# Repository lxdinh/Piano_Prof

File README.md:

# CODING AGENTS: READ THIS FIRST

This is a **handoff bundle** from Claude Design (claude.ai/design).

A user mocked up designs in HTML/CSS/JS using an AI design tool, then exported this bundle so a coding agent can implement the designs for real.

## What you should do — IMPORTANT

**Read `piano-professor-v3/project/Piano Professor.html` in full.** The user had this file open when they triggered the handoff, so it's almost certainly the primary design they want built. Read it top to bottom — don't skim. Then **follow its imports**: open every file it pulls in (shared components, CSS, scripts) so you understand how the pieces fit together before you start implementing.

**If anything is ambiguous, ask the user to confirm before you start implementing.** It's much cheaper to clarify scope up front than to build the wrong thing.

## About the design files

The design medium is **HTML/CSS/JS** — these are prototypes, not production code. Your job is to **recreate them pixel-perfectly** in whatever technology makes sense for the target codebase (React, Vue, native, whatever fits). Match the visual output; don't copy the prototype's internal structure unless it happens to fit.

**Don't render these files in a browser or take screenshots unless the user asks you to.** Everything you need — dimensions, colors, layout rules — is spelled out in the source. Read the HTML and CSS directly; a screenshot won't tell you anything they don't.

## Bundle contents

- `piano-professor-v3/README.md` — this file
- `piano-professor-v3/project/` — the `Piano Professor V3` project files (HTML prototypes, assets, components)

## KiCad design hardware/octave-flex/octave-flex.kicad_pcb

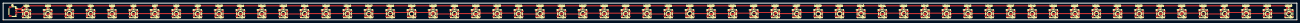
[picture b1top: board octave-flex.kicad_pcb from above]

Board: 2 copper layers, 831.3 x 10.7 mm, 121 parts (0 on the bottom side), 62 nets.

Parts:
C1, C2, C3, C4, C5, C6, C7, C8, C9, C10, C11, C12, C13, C14, C15, C16, C17, C18, C19, C20, C21, C22, C23, C24, C25, C26, C27, C28, C29, C30, C31, C32, C33, C34, C35, C36, C37, C38, C39, C40, C41, C42, C43, C44, C45, C46, C47, C48, C49, C50, C51, C52, C53, C54, C55, C56, C57, C58, C59, C60: 100nF; C_0603_1608Metric
J1: JST_SH_4P; JST_SH_SM04B-SRSS-TB_1x04-1MP_P1.00mm_Horizontal
LED1, LED2, LED3, LED4, LED5, LED6, LED7, LED8, LED9, LED10, LED11, LED12, LED13, LED14, LED15, LED16, LED17, LED18, LED19, LED20, LED21, LED22, LED23, LED24, LED25, LED26, LED27, LED28, LED29, LED30, LED31, LED32, LED33, LED34, LED35, LED36, LED37, LED38, LED39, LED40, LED41, LED42, LED43, LED44, LED45, LED46, LED47, LED48, LED49, LED50, LED51, LED52, LED53, LED54, LED55, LED56, LED57, LED58, LED59, LED60: WS2812B-B/W; LED-SMD_4P-L5.0-W5.0-TL_WS2812B-B

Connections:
+5V: C1.1, C2.1, C3.1, C4.1, C5.1, C6.1, C7.1, C8.1, C9.1, C10.1, C11.1, C12.1, C13.1, C14.1, C15.1, C16.1, C17.1, C18.1, C19.1, C20.1, C21.1, C22.1, C23.1, C24.1, C25.1, C26.1, C27.1, C28.1, C29.1, C30.1, C31.1, C32.1, C33.1, C34.1, C35.1, C36.1, C37.1, C38.1, C39.1, C40.1, C41.1, C42.1, C43.1, C44.1, C45.1, C46.1, C47.1, C48.1, C49.1, C50.1, C51.1, C52.1, C53.1, C54.1, C55.1, C56.1, C57.1, C58.1, C59.1, C60.1, J1.1, LED1.1 (VDD), LED2.1 (VDD), LED3.1 (VDD), LED4.1 (VDD), LED5.1 (VDD), LED6.1 (VDD), LED7.1 (VDD), LED8.1 (VDD), LED9.1 (VDD), LED10.1 (VDD), LED11.1 (VDD), LED12.1 (VDD), LED13.1 (VDD), LED14.1 (VDD), LED15.1 (VDD), LED16.1 (VDD), LED17.1 (VDD), LED18.1 (VDD), LED19.1 (VDD), LED20.1 (VDD), LED21.1 (VDD), LED22.1 (VDD), LED23.1 (VDD), LED24.1 (VDD), LED25.1 (VDD), LED26.1 (VDD), LED27.1 (VDD), LED28.1 (VDD), LED29.1 (VDD), LED30.1 (VDD), LED31.1 (VDD), LED32.1 (VDD), LED33.1 (VDD), LED34.1 (VDD), LED35.1 (VDD), LED36.1 (VDD), LED37.1 (VDD), LED38.1 (VDD), LED39.1 (VDD), LED40.1 (VDD), LED41.1 (VDD), LED42.1 (VDD), LED43.1 (VDD), LED44.1 (VDD), LED45.1 (VDD), LED46.1 (VDD), LED47.1 (VDD), LED48.1 (VDD), LED49.1 (VDD), LED50.1 (VDD), LED51.1 (VDD), LED52.1 (VDD), LED53.1 (VDD), LED54.1 (VDD), LED55.1 (VDD), LED56.1 (VDD), LED57.1 (VDD), LED58.1 (VDD), LED59.1 (VDD), LED60.1 (VDD)
/DIN_IN: J1.3, LED1.4 (DIN)
GND: C1.2, C2.2, C3.2, C4.2, C5.2, C6.2, C7.2, C8.2, C9.2, C10.2, C11.2, C12.2, C13.2, C14.2, C15.2, C16.2, C17.2, C18.2, C19.2, C20.2, C21.2, C22.2, C23.2, C24.2, C25.2, C26.2, C27.2, C28.2, C29.2, C30.2, C31.2, C32.2, C33.2, C34.2, C35.2, C36.2, C37.2, C38.2, C39.2, C40.2, C41.2, C42.2, C43.2, C44.2, C45.2, C46.2, C47.2, C48.2, C49.2, C50.2, C51.2, C52.2, C53.2, C54.2, C55.2, C56.2, C57.2, C58.2, C59.2, C60.2, J1.2, LED1.3 (VSS), LED2.3 (VSS), LED3.3 (VSS), LED4.3 (VSS), LED5.3 (VSS), LED6.3 (VSS), LED7.3 (VSS), LED8.3 (VSS), LED9.3 (VSS), LED10.3 (VSS), LED11.3 (VSS), LED12.3 (VSS), LED13.3 (VSS), LED14.3 (VSS), LED15.3 (VSS), LED16.3 (VSS), LED17.3 (VSS), LED18.3 (VSS), LED19.3 (VSS), LED20.3 (VSS), LED21.3 (VSS), LED22.3 (VSS), LED23.3 (VSS), LED24.3 (VSS), LED25.3 (VSS), LED26.3 (VSS), LED27.3 (VSS), LED28.3 (VSS), LED29.3 (VSS), LED30.3 (VSS), LED31.3 (VSS), LED32.3 (VSS), LED33.3 (VSS), LED34.3 (VSS), LED35.3 (VSS), LED36.3 (VSS), LED37.3 (VSS), LED38.3 (VSS), LED39.3 (VSS), LED40.3 (VSS), LED41.3 (VSS), LED42.3 (VSS), LED43.3 (VSS), LED44.3 (VSS), LED45.3 (VSS), LED46.3 (VSS), LED47.3 (VSS), LED48.3 (VSS), LED49.3 (VSS), LED50.3 (VSS), LED51.3 (VSS), LED52.3 (VSS), LED53.3 (VSS), LED54.3 (VSS), LED55.3 (VSS), LED56.3 (VSS), LED57.3 (VSS), LED58.3 (VSS), LED59.3 (VSS), LED60.3 (VSS)
unnamed: LED1.2 (DOUT), LED2.4 (DIN)
unnamed: LED2.2 (DOUT), LED3.4 (DIN)
unnamed: LED3.2 (DOUT), LED4.4 (DIN)
unnamed: LED4.2 (DOUT), LED5.4 (DIN)
unnamed: LED5.2 (DOUT), LED6.4 (DIN)
unnamed: LED6.2 (DOUT), LED7.4 (DIN)
unnamed: LED7.2 (DOUT), LED8.4 (DIN)
unnamed: LED8.2 (DOUT), LED9.4 (DIN)
unnamed: LED9.2 (DOUT), LED10.4 (DIN)
unnamed: LED10.2 (DOUT), LED11.4 (DIN)
unnamed: LED11.2 (DOUT), LED12.4 (DIN)
unnamed: LED12.2 (DOUT), LED13.4 (DIN)
unnamed: LED13.2 (DOUT), LED14.4 (DIN)
unnamed: LED14.2 (DOUT), LED15.4 (DIN)
unnamed: LED15.2 (DOUT), LED16.4 (DIN)
unnamed: LED16.2 (DOUT), LED17.4 (DIN)
unnamed: LED17.2 (DOUT), LED18.4 (DIN)
unnamed: LED18.2 (DOUT), LED19.4 (DIN)
unnamed: LED19.2 (DOUT), LED20.4 (DIN)
unnamed: LED20.2 (DOUT), LED21.4 (DIN)
unnamed: LED21.2 (DOUT), LED22.4 (DIN)
unnamed: LED22.2 (DOUT), LED23.4 (DIN)
unnamed: LED23.2 (DOUT), LED24.4 (DIN)
unnamed: LED24.2 (DOUT), LED25.4 (DIN)
unnamed: LED25.2 (DOUT), LED26.4 (DIN)
unnamed: LED26.2 (DOUT), LED27.4 (DIN)
unnamed: LED27.2 (DOUT), LED28.4 (DIN)
unnamed: LED28.2 (DOUT), LED29.4 (DIN)
unnamed: LED29.2 (DOUT), LED30.4 (DIN)
unnamed: LED30.2 (DOUT), LED31.4 (DIN)
unnamed: LED31.2 (DOUT), LED32.4 (DIN)
unnamed: LED32.2 (DOUT), LED33.4 (DIN)
unnamed: LED33.2 (DOUT), LED34.4 (DIN)
unnamed: LED34.2 (DOUT), LED35.4 (DIN)
unnamed: LED35.2 (DOUT), LED36.4 (DIN)
unnamed: LED36.2 (DOUT), LED37.4 (DIN)
unnamed: LED37.2 (DOUT), LED38.4 (DIN)
unnamed: LED38.2 (DOUT), LED39.4 (DIN)
unnamed: LED39.2 (DOUT), LED40.4 (DIN)
unnamed: LED40.2 (DOUT), LED41.4 (DIN)
unnamed: LED41.2 (DOUT), LED42.4 (DIN)
unnamed: LED42.2 (DOUT), LED43.4 (DIN)
unnamed: LED43.2 (DOUT), LED44.4 (DIN)
unnamed: LED44.2 (DOUT), LED45.4 (DIN)
unnamed: LED45.2 (DOUT), LED46.4 (DIN)
unnamed: LED46.2 (DOUT), LED47.4 (DIN)
unnamed: LED47.2 (DOUT), LED48.4 (DIN)
unnamed: LED48.2 (DOUT), LED49.4 (DIN)
unnamed: LED49.2 (DOUT), LED50.4 (DIN)
unnamed: LED50.2 (DOUT), LED51.4 (DIN)
unnamed: LED51.2 (DOUT), LED52.4 (DIN)
unnamed: LED52.2 (DOUT), LED53.4 (DIN)
unnamed: LED53.2 (DOUT), LED54.4 (DIN)
unnamed: LED54.2 (DOUT), LED55.4 (DIN)
unnamed: LED55.2 (DOUT), LED56.4 (DIN)
unnamed: LED56.2 (DOUT), LED57.4 (DIN)
unnamed: LED57.2 (DOUT), LED58.4 (DIN)
unnamed: LED58.2 (DOUT), LED59.4 (DIN)
unnamed: LED59.2 (DOUT), LED60.4 (DIN)

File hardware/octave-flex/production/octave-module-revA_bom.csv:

Designator,Footprint,Quantity,Value,LCSC Part #
"C1, C10, C11, C12, C13, C14, C15, C16, C17, C18, C19, C2, C20, C21, C22, C23, C24, C25, C26, C27, C28, C29, C3, C30, C31, C32, C33, C34, C35, C36, C37, C38, C39, C4, C40, C41, C42, C43, C44, C45, C46, C47, C48, C49, C5, C50, C51, C52, C53, C54, C55, C56, C57, C58, C59, C6, C60, C7, C8, C9",0603,60,100nF,C14663
J1,JST_SH_SM04B-SRSS-TB_1x04-1MP_P1.00mm_Horizontal,1,JST_SH_4P,C160404
"LED1, LED10, LED11, LED12, LED13, LED14, LED15, LED16, LED17, LED18, LED19, LED2, LED20, LED21, LED22, LED23, LED24, LED25, LED26, LED27, LED28, LED29, LED3, LED30, LED31, LED32, LED33, LED34, LED35, LED36, LED37, LED38, LED39, LED4, LED40, LED41, LED42, LED43, LED44, LED45, LED46, LED47, LED48, LED49, LED5, LED50, LED51, LED52, LED53, LED54, LED55, LED56, LED57, LED58, LED59, LED6, LED60, LED7, LED8, LED9",LED-SMD_4P-L5.0-W5.0-TL_WS2812B-B,60,WS2812B-B/W,C114586

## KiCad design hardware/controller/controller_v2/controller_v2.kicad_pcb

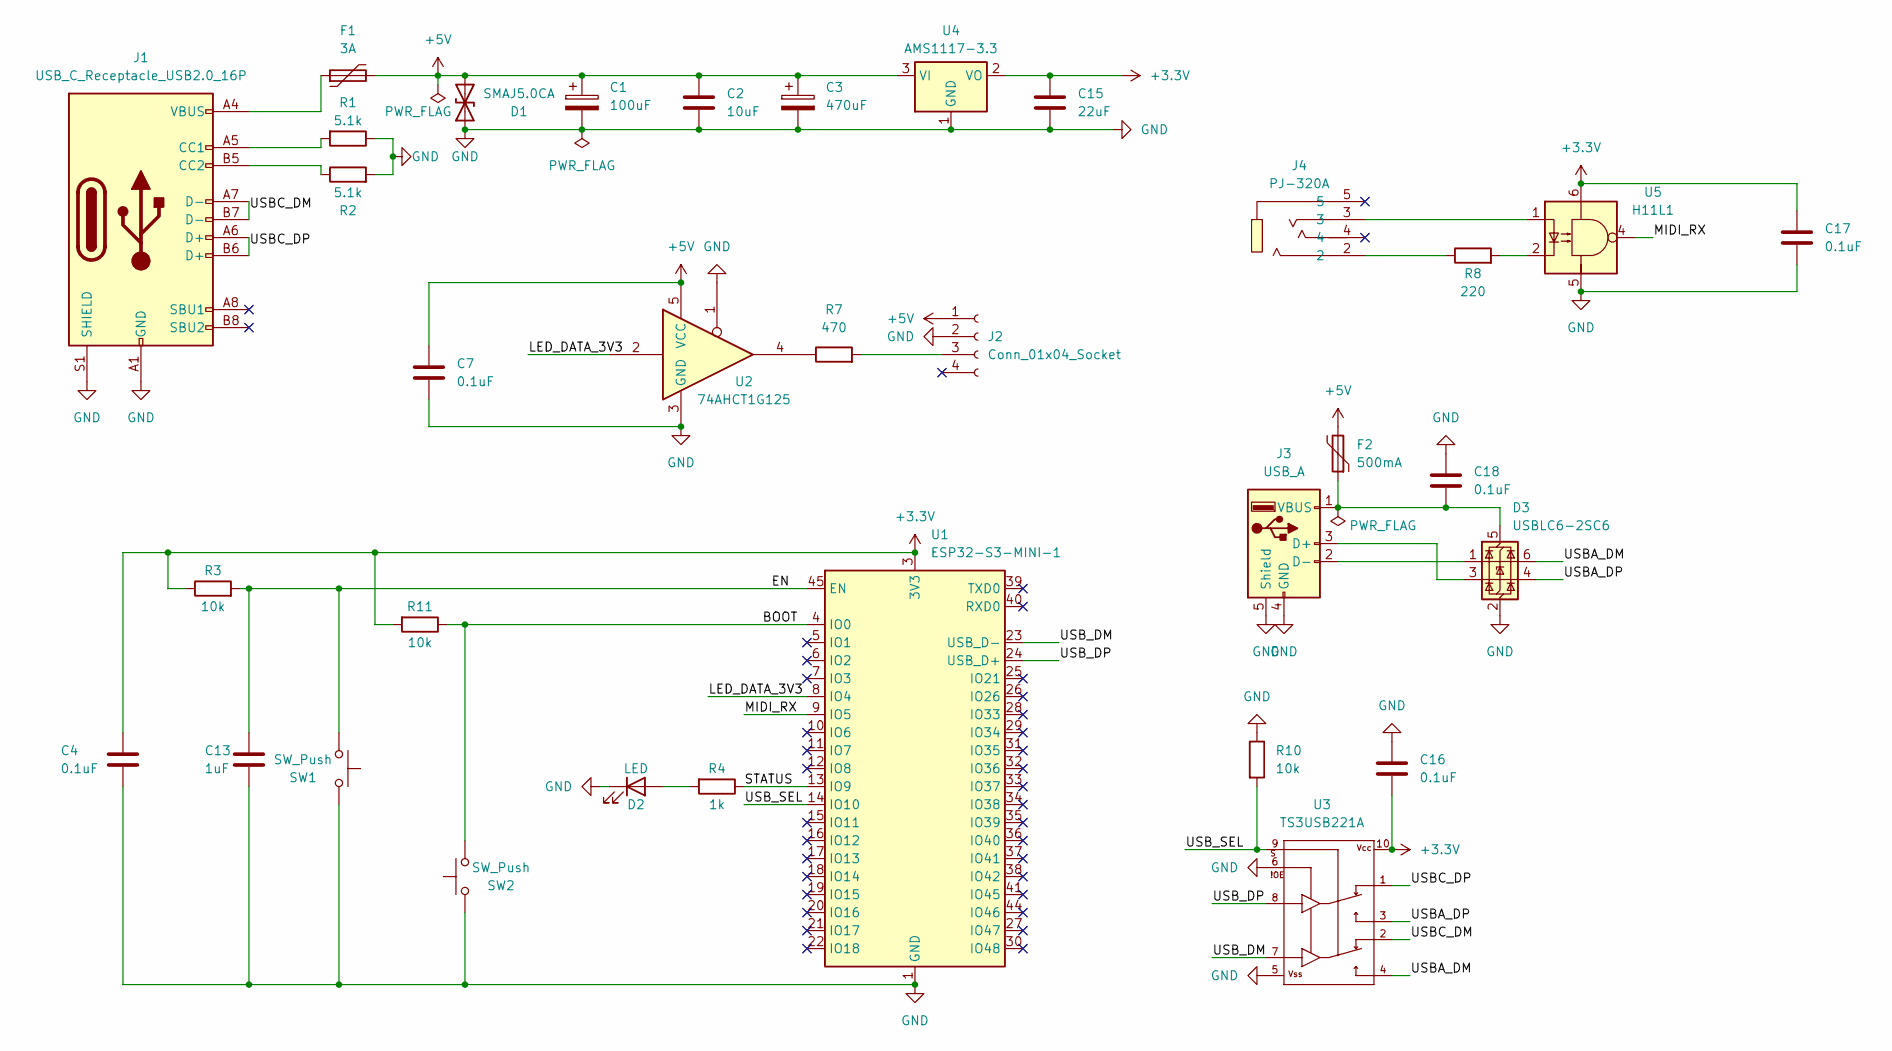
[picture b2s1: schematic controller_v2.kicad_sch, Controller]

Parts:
C1: 100uF; CP_Elec_6.3x5.4
C2: 10uF; C_0805_2012Metric
C3: 470uF; CP_Elec_8x10.5
C4, C7, C16, C17, C18: 0.1uF; C_0603_1608Metric
C13: 1uF; C_0603_1608Metric
C15: 22uF; C_0805_2012Metric
D1: SMAJ5.0CA; D_SMA
D2: LED; LED_0603_1608Metric
D3: USBLC6-2SC6; SOT-23-6
F1: 3A; Fuse_1812_4532Metric
F2: 500mA; Fuse_1206_3216Metric
J1: USB_C_Receptacle_USB2.0_16P; USB_C_Receptacle_GCT_USB4105-xx-A_16P_TopMnt_Horizontal
J2: Conn_01x04_Socket; JST_SH_SM04B-SRSS-TB_1x04-1MP_P1.00mm_Horizontal
J3: USB_A; USB_A_TE_292303-7_Horizontal
J4: PJ-320A; AUDIO-TH_XKB_PJ-320A; MPN PJ-320A; LCSC Part C2884926
R1, R2: 5.1k; R_0603_1608Metric
R3, R10, R11: 10k; R_0603_1608Metric
R4: 1k; R_0603_1608Metric
R7: 470; R_0603_1608Metric
R8: 220; R_0603_1608Metric
SW1, SW2: SW_Push; SW_SPST_PTS645Sx43SMTR92
U1: ESP32-S3-MINI-1; ESP32-S2-MINI-1
U2: 74AHCT1G125; SOT-23-5
U3: TS3USB221A; QFN-10-RSE
U4: AMS1117-3.3; SOT-223-3_TabPin2
U5: H11L1; IC_H11L1SM

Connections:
+3.3V: C4.1, C15.1, C16.2, C17.2, R3.1, R11.2, U1.3 (3V3), U3.10, U4.2 (VO), U5.6; also elsewhere on the board
+5V: C1.1, C2.1, C3.1, C7.1, D1.2 (A2), F1.2, F2.2, J2.1, U2.5 (VCC), U4.3 (VI)
/BOOT: R11.1, SW2.2, U1.4 (IO0)
/EN: C13.1, R3.2, SW1.1, U1.45 (EN)
/LED_DATA_3V3: U1.8 (IO4), U2.2
/MIDI_RX: U1.9 (IO5), U5.4; also elsewhere on the board
/STATUS: R4.1, U1.13 (IO9)
/USBA_DM: D3.6 (I/O1), U3.4
/USBA_DP: D3.4 (I/O2), U3.3
/USBC_DM: J1.A7 (D-), J1.B7 (D-), U3.2
/USBC_DP: J1.A6 (D+), J1.B6 (D+), U3.1
/USB_DM: U1.23 (USB_D-), U3.7
/USB_DP: U1.24 (USB_D+), U3.8
/USB_SEL: R10.2, U1.14 (IO10), U3.9
GND: C1.2, C2.2, C3.2, C4.2, C7.2, C13.2, C15.2, C16.1, C17.1, C18.2, D1.1 (A1), D2.1 (K), D3.2 (GND), J1.A1 (GND), J1.A12 (GND), J1.B1 (GND), J1.B12 (GND), J1.S1 (SHIELD), J2.2, J3.4 (GND), J3.5 (Shield), R1.1, R2.2, R10.1, SW1.2, SW2.1, U1.1 (GND), U1.2 (GND), U1.42 (GND), U1.43 (GND), U1.46 (GND), U1.47 (GND), U1.48 (GND), U1.49 (GND), U1.50 (GND), U1.51 (GND), U1.52 (GND), U1.53 (GND), U1.54 (GND), U1.55 (GND), U1.56 (GND), U1.57 (GND), U1.58 (GND), U1.59 (GND), U1.60 (GND), U1.61 (GND), U1.62 (GND), U1.63 (GND), U1.64 (GND), U1.65 (GND), U2.1, U2.3 (GND), U3.5, U3.6, U4.1 (GND), U5.5
unnamed: D2.2 (A), R4.2
unnamed: C18.1, D3.5 (VBUS), F2.1, J3.1 (VBUS)
unnamed: F1.1, J1.A4 (VBUS), J1.A9 (VBUS), J1.B4 (VBUS), J1.B9 (VBUS)
unnamed: J1.A5 (CC1), R1.2
unnamed: J1.B5 (CC2), R2.1
unnamed: J2.3, R7.2
unnamed: D3.3 (I/O2), J3.3 (D+)
unnamed: D3.1 (I/O1), J3.2 (D-)
unnamed: J4.2, R8.1
unnamed: J4.3, U5.1
unnamed: R7.1, U2.4
unnamed: R8.2, U5.2

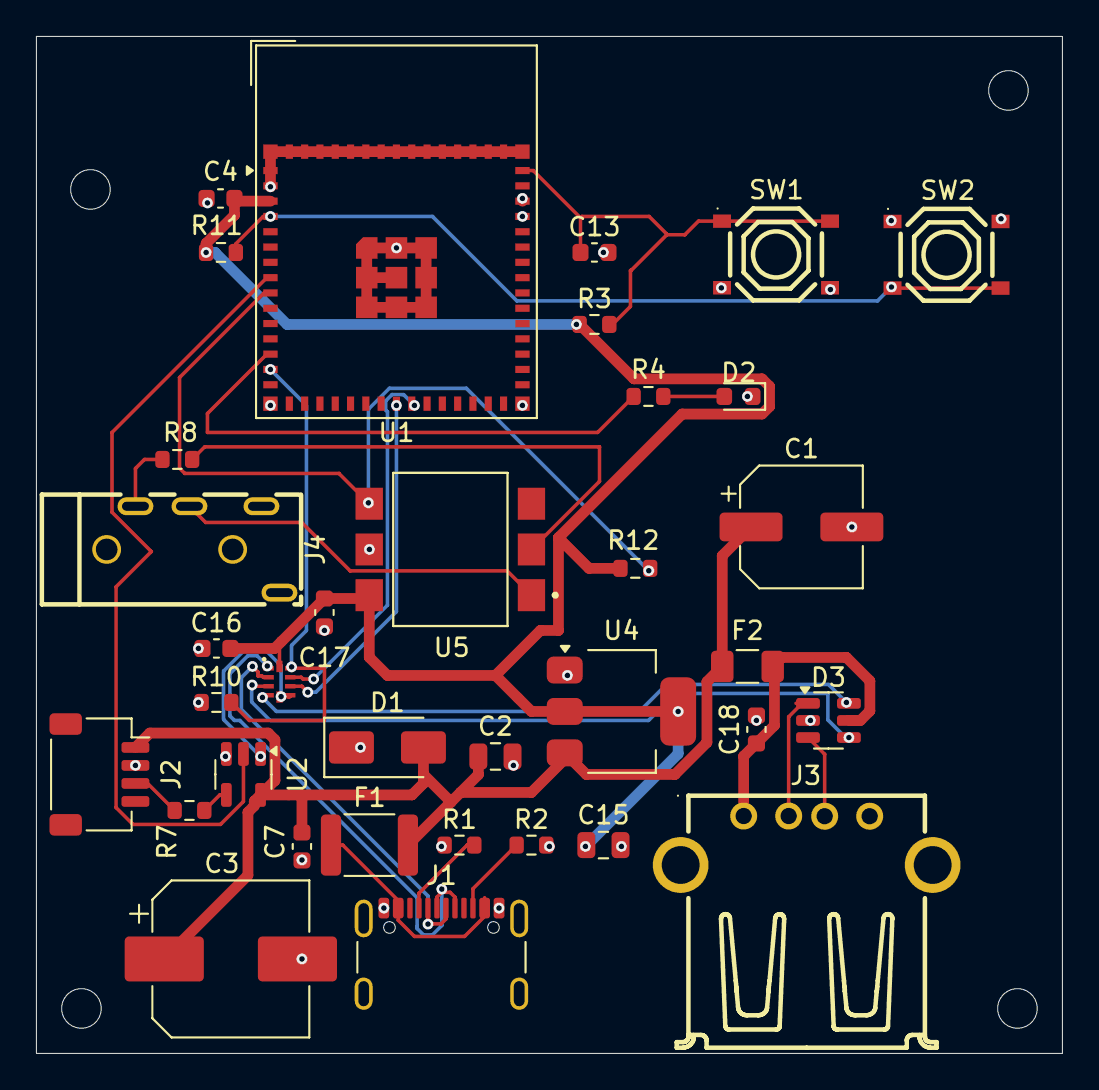
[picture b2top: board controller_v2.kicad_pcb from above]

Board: 2 copper layers, 57.0 x 56.5 mm, 35 parts (0 on the bottom side), 27 nets.

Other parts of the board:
R12: 1k; R_0603_1608Metric

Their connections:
+3.3V: R12.1; also elsewhere on the board
/MIDI_RX: R12.2; also elsewhere on the board

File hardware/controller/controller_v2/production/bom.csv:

Designator,Footprint,Quantity,Value,LCSC Part #
C1,CP_Elec_6.3x5.4,1,100uF,C44638
C13,0603,1,1uF,C15849
C15,0805,1,22uF,C45783
"C16, C17, C18, C4, C7",0603,5,0.1uF,C14663
C2,0805,1,10uF,C15850
C3,CP_Elec_8x10.5,1,470uF,C42599
D1,D_SMA,1,SMAJ5.0CA,C202221
D2,0603,1,LED,C72043
D3,SOT-23-6,1,USBLC6-2SC6,C7519
F1,1812,1,3A,C190053
F2,1206,1,500mA,C106264
J1,USB_C_Receptacle_GCT_USB4105-xx-A_16P_TopMnt_Horizontal,1,USB_C_Receptacle_USB2.0_16P,C165948
J2,JST_SH_SM04B-SRSS-TB_1x04-1MP_P1.00mm_Horizontal,1,Conn_01x04_Socket,C160403
J3,USB_A_TE_292303-7_Horizontal,1,USB_A,C86461
J4,AUDIO-TH_XKB_PJ-320A,1,PJ-320A,C2884926
"R1, R2",0603,2,5.1k,C23186
"R10, R11, R3",0603,3,10k,C25804
R4,0603,1,1k,C21190
R7,0603,1,470,C23179
R8,0603,1,220,C22962
"SW1, SW2",SW_SPST_PTS645Sx43SMTR92,2,SW_Push,C318884
U1,ESP32-S2-MINI-1,1,ESP32-S3-MINI-1,C3013941
U2,SOT-23-5,1,74AHCT1G125,C7484
U3,QFN-10-RSE,1,TS3USB221A,C128396
U4,SOT-223-3_TabPin2,1,AMS1117-3.3,C6186
U5,IC_H11L1SM,1,H11L1,C78589

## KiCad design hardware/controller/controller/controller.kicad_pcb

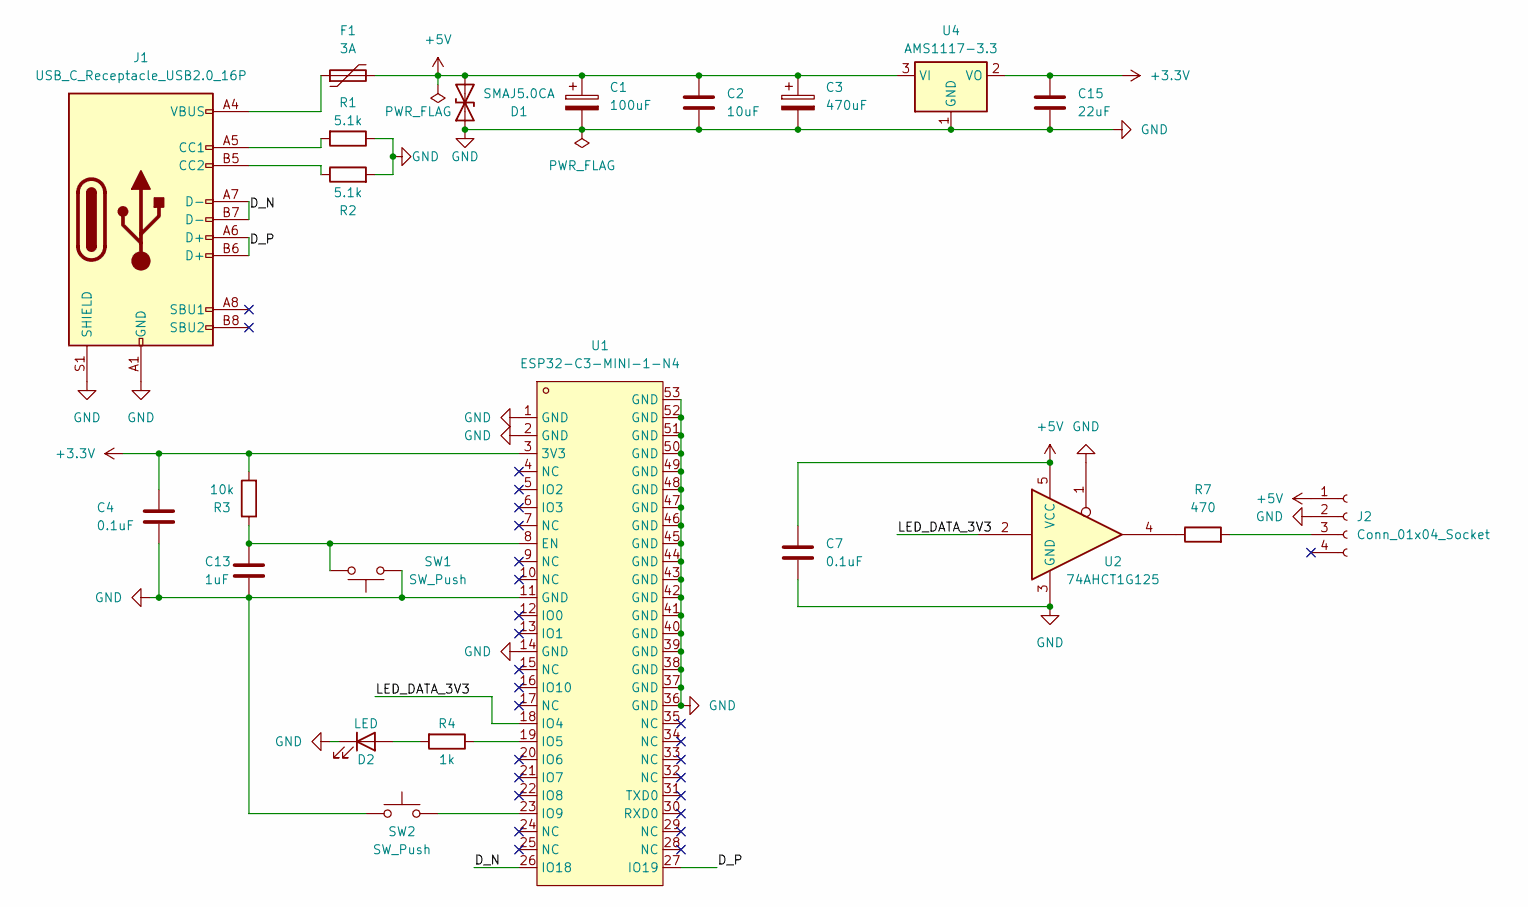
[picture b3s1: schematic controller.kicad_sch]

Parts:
C1: 100uF; CP_Elec_6.3x5.4
C2: 10uF; C_0805_2012Metric
C3: 470uF; CP_Elec_8x10.5
C4, C7: 0.1uF; C_0603_1608Metric
C13: 1uF; C_0603_1608Metric
C15: 22uF; C_0805_2012Metric
D1: SMAJ5.0CA; D_SMA
D2: LED; LED_0603_1608Metric
F1: 3A; Fuse_1812_4532Metric
J1: USB_C_Receptacle_USB2.0_16P; USB_C_Receptacle_GCT_USB4105-xx-A_16P_TopMnt_Horizontal
J2: Conn_01x04_Socket; JST_SH_SM04B-SRSS-TB_1x04-1MP_P1.00mm_Horizontal
R1, R2: 5.1k; R_0603_1608Metric
R3: 10k; R_0603_1608Metric
R4: 1k; R_0603_1608Metric
R7: 470; R_0603_1608Metric
SW1, SW2: SW_Push; SW_SPST_PTS645Sx43SMTR92
U1: ESP32-C3-MINI-1-N4; WIFIM-SMD_ESP32-C3-MINI-1; MPN ESP32-C3-MINI-1-N4; LCSC Part C2838502
U2: 74AHCT1G125; SOT-23-5
U4: AMS1117-3.3; SOT-223-3_TabPin2

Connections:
+3.3V: C4.1, C15.1, R3.2, U1.3 (3V3), U4.2 (VO)
+5V: C1.1, C2.1, C3.1, C7.1, D1.2 (A2), F1.2, J2.1, U2.5 (VCC), U4.3 (VI)
/D_N: J1.A7 (D-), J1.B7 (D-), U1.26 (IO18)
/D_P: J1.A6 (D+), J1.B6 (D+), U1.27 (IO19)
/LED_DATA_3V3: U1.18 (IO4), U2.2
GND: C1.2, C2.2, C3.2, C4.2, C7.2, C13.2, C15.2, D1.1 (A1), D2.1 (K), J1.A1 (GND), J1.A12 (GND), J1.B1 (GND), J1.B12 (GND), J1.S1 (SHIELD), J2.2, R1.1, R2.2, SW1.1, SW2.1, U1.1 (GND), U1.2 (GND), U1.11 (GND), U1.14 (GND), U1.36 (GND), U1.37 (GND), U1.38 (GND), U1.39 (GND), U1.40 (GND), U1.41 (GND), U1.42 (GND), U1.43 (GND), U1.44 (GND), U1.45 (GND), U1.46 (GND), U1.47 (GND), U1.48 (GND), U1.49 (GND), U1.50 (GND), U1.51 (GND), U1.52 (GND), U1.53 (GND), U2.1, U2.3 (GND), U4.1 (GND)
unnamed: D2.2 (A), R4.2
unnamed: F1.1, J1.A4 (VBUS), J1.A9 (VBUS), J1.B4 (VBUS), J1.B9 (VBUS)
unnamed: J1.A5 (CC1), R1.2
unnamed: J1.B5 (CC2), R2.1
unnamed: J2.3, R7.2
unnamed: R7.1, U2.4
unnamed: C13.1, R3.1, SW1.2, U1.8 (EN)
unnamed: R4.1, U1.19 (IO5)
unnamed: SW2.2, U1.23 (IO9)

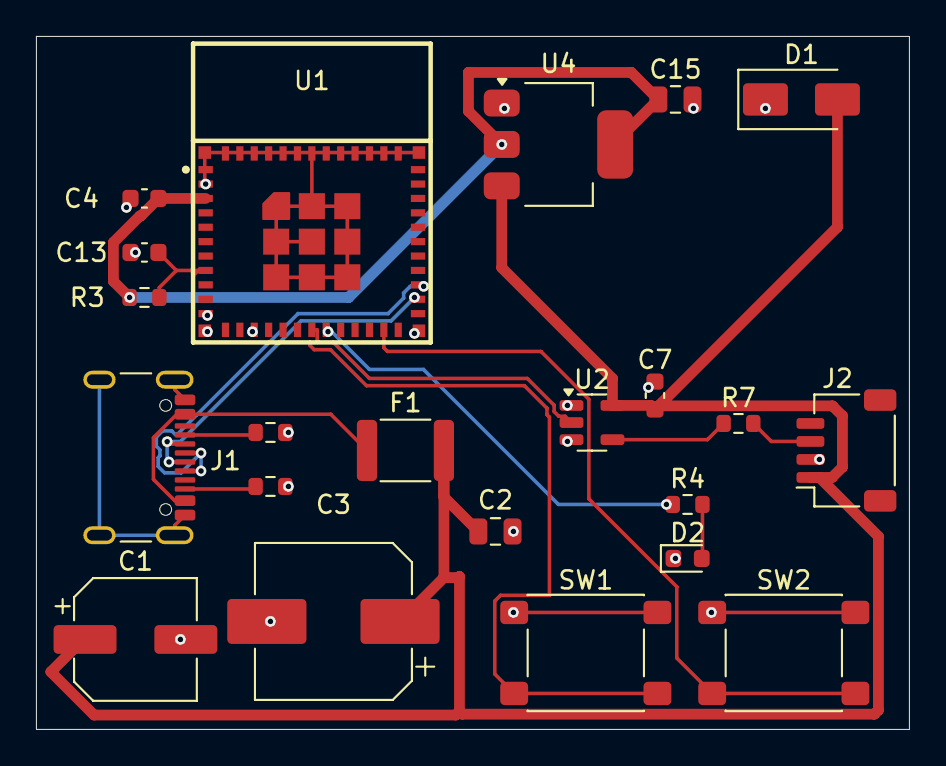
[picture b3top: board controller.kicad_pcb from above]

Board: 2 copper layers, 48.5 x 38.5 mm, 22 parts (0 on the bottom side), 15 nets.

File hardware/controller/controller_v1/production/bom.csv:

Designator,Footprint,Quantity,Value,LCSC Part #
C1,CP_Elec_6.3x5.4,1,100uF,
C13,0603,1,1uF,
C15,0805,1,22uF,
C2,0805,1,10uF,
C3,CP_Elec_8x10.5,1,470uF,
"C4, C7",0603,2,0.1uF,
D1,D_SMA,1,SMAJ5.0CA,
D2,0603,1,LED,
F1,1812,1,3A,
J1,USB_C_Receptacle_GCT_USB4105-xx-A_16P_TopMnt_Horizontal,1,USB_C_Receptacle_USB2.0_16P,
J2,JST_SH_SM04B-SRSS-TB_1x04-1MP_P1.00mm_Horizontal,1,Conn_01x04_Socket,
"R1, R2",0603,2,5.1k,
R3,0603,1,10k,
R4,0603,1,1k,
R7,0603,1,470,
"SW1, SW2",SW_SPST_PTS645Sx43SMTR92,2,SW_Push,
U1,WIFIM-SMD_ESP32-C3-MINI-1,1,ESP32-C3-MINI-1-N4,C2838502
U2,SOT-23-5,1,74AHCT1G125,
U4,SOT-223-3_TabPin2,1,AMS1117-3.3,

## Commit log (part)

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2026-05-22 Claude Design handoff: Piano Professor
2026-05-22 feat: add BLE pairing screen + Supabase schema
    Implements the two foundational components requested in the architecture doc:
    1. supabase/migrations/001_initial_schema.sql — full PostgreSQL schema
    - 20+ tables: profiles, lessons, xp_log, streaks, hearts, quests,
    achievements, songs, ble_devices, uploaded_sheets, leagues, etc.
    - Stored functions: complete_lesson(), consume_heart(), award_xp(),
    update_streak(), handle_new_user() (auth trigger)
2026-05-23 fix: downgrade flutter_soloud to ^2.1.0 to resolve meta version conflict
    flutter_soloud >=2.1.1 requires meta ^1.15.0 which conflicts with
    flutter_test SDK pinning meta to 1.12.0. Pin to ^2.1.0 to unblock CI.
    https://claude.ai/code/session_01SuMh7hfqoHogAuCY332TVw
2026-05-23 fix(ci): downgrade Gradle 9.1→8.12 to fix groovy.xml.QName
    Gradle 9.x bundles Groovy 4.x which removed groovy.xml.QName.
    Flutter's flutter.groovy still imports it, causing the build to fail.
    Gradle 8.12 uses Groovy 3.x (class present) and satisfies the
    AGP 9.0.1 minimum requirement of Gradle 8.10.2+.
    https://claude.ai/code/session_01SuMh7hfqoHogAuCY332TVw
2026-05-23 fix(android): use task-level compilerOptions DSL for Kotlin 2.x
    kotlinOptions was removed as a hard error in Kotlin 2.x.
    task-level compilerOptions on KotlinJvmCompile works without
    requiring the kotlin{} project extension (which needs explicit
    plugin application).
    https://claude.ai/code/session_01SuMh7hfqoHogAuCY332TVw
2026-05-28 feat(app): rebuild Piano Professor as a React Native + Expo app
    Replace the Flutter (mobile/) and Kotlin (App/) apps — both moved to
    legacy/ — with a TypeScript React Native app built on the existing Expo +
    EAS pipeline, preserving the cream/Duolingo-green/mascot prototype design.
    What's included:
    - 5-tab shell (Learn / Path / Songbook / Profile / Settings) via
    @react-navigation native-stack + bottom-tabs (no Reanimated).
2026-05-28 feat(polish 1.2): signature components — chunky buttons, animated counters
    The first wave of pieces every screen depends on, upgraded for premium feel:
    - ChunkyButton: gradient face + a real "shadow plate" underneath. PressIn
    springs the face down by 5px (revealing the shadow shrinking to 0), then
    springs back on PressOut. Fires haptic on each press. Loading state baked
    in. New `violet` variant.
    - AnimatedCounter: smoothly ticks XP / streak / gems instead of snapping —
2026-05-28 feat(polish 1.4): realistic piano + glowing LED strip
    PianoKeyboard rebuilt with mobile-grade depth + premium light effects:
    - White keys: ivory gradient with a top inner-shadow and rounded-fillet
    bottom; thin shadow lines between adjacent keys.
    - Black keys: 3-stop dark gradient + a top highlight strip to fake the
    shaped plastic of a real key.
    - Lit-key glow: animated Animated.View overlays positioned exactly over
2026-05-28 feat(polish 1.7): Path — winding Duolingo trail with pulsing active node
    The path tab now renders as sections (one per grade) with a wandering
    6-lane zig-zag of physical-feeling nodes:
    - Per-grade section header — pill with grade number + title, bracketed
    by hairlines so the path reads as chapters.
    - Nodes: chunky gradient pucks with a shadow plate (press → drops down
    4px). Color per state — butter gold for completed, brand green for
2026-05-28 feat(polish 1.9): celebrations — confetti, staged star pops, fanfare
    Lesson-complete is now an event:
    - Confetti rain (60 native-driven pieces, color-cycling, fading at top/
    bottom of the screen, slight horizontal sway + 720° rotation).
    - Title + trophy mascot lift in on a 500ms entrance.
    - Stars pop one at a time at 280ms intervals — each spring-scales from 0
    with a rotate-into-place. Bump haptic per filled star.
2026-05-28 feat(mascot): wire 13 real Maestro Penguini PNGs into app moods
    User uploaded 41 mascot poses with their own naming. Mapped the 13 the
    app actually renders to their files (best thematic fit):
    happy→teach, wave→welcome-cutout, thinking→idea, wow→wow, sad→sad,
    sleepy→tired, laugh→showman, wink→star, cheer→cheer, love→love,
    shocked→shocked, cool→cool, trophy→trophy.
    Verified: tsc clean, Metro bundles all 13 images (~4MB). The SVG penguin
2026-05-28 Piano Professor React Native rebuild — full app v1
    Complete React Native + Expo SDK 52 rebuild: navigation, gamification, lesson engine, mascot system, BLE integration, all 5 screens polished.
2026-05-28 ci: update build info [skip ci]
2026-05-29 fix(ci): parse EAS build URL from "See logs:" line
    Previous regex looked for "buildDetailsPageUrl" which eas-cli doesn't
    emit on --no-wait. Now we grep the canonical expo.dev URL directly, with
    a JSON-id reconstruction fallback. Also clarifies the message written
    to last-build-url.txt — users open this URL on their phone to install.
2026-05-29 feat(ui): premium treatment for Learn, Lesson, and Profile
    FloatingNotes now configurable (travel, startBottom, colors, glyphSize,
    maxOpacity) so it works as a header band and on the dark lesson stage.
    Learn:
    - 3-stop cream→butter header gradient with faint drifting notes
    - Daily-goal ring sits inside a HeroHalo (gold, or green when goal hit)
    - Sparkles burst around the ring when the daily goal is reached
2026-05-29 feat: landscape lessons + full piano + 4-tab pathway app
    Tabs (Learn / Sheet / Practice / Profile):
    - Replaces 5-tab nav. Settings moves to a gear on Profile (root stack).
    - Practice is a brand-new free-play landscape screen with the full keyboard
    and quick chord triggers (C, G, Am, F).
    Landscape lessons:
    - LessonScreen rebuilt to match the design screenshot: cream paper, top bar
2026-05-29 Add index.html to legacy/ web UI folder
2026-05-29 Strip audio from legacy/ web UI (keep visual piano + LEDs + lessons)
2026-05-30 docs: add CLAUDE.md — session continuity notes
    Captures: current branch/PR state, EAS build pipeline + last build URL,
    tech-stack do/don't list, source map, critical invariants (local dates,
    ProgressBackend, step-gated engine, landscape-on-demand, mascot mapping),
    and the next-session priority — port UI from legacy/ at high fidelity.
2026-05-30 Sleek lesson layout, clean mascots, smooth full-range piano audio
    Layout: derive the keyboard height from the space left after the top bar,
    teacher row, and controls (cap 180, down from 230) and bottom-anchor it, so
    the keys no longer overlap the REPLAY/CONTINUE buttons. Slim the lesson
    mascot to a 68px avatar.
    Mascot art: strip the stray sliver bleeding in from the neighbouring sticker
    above each cutout (the fragment that showed over the penguin's head). Removes
2026-05-30 Fix piano keyboard: real multi-touch polyphony, reliable sound + haptics
    The on-screen keyboard rendered one <Pressable> per key in an absolute-
    positioned overlay. React Native's gesture-responder system only grants the
    active responder to one or two overlapping views at a time, which caused the
    reported bugs:
    - couldn't sound more than ~2 notes at once, so chords were impossible
    - many keys (notably the black keys overlapping the white tap targets) never
2026-05-31 Fix piano touch deadzone, CONTINUE button, practice layout + hand colors
    - PianoKeyboard: hit-test taps from window-absolute pageX/pageY (measured
    origin) instead of locationX. On Android, locationX was reported relative
    to the SVG sub-view under each touch, so the right half of the keyboard
    resolved to no key and played no sound. Now reliable edge to edge.
    - ChunkyButton: disabled state is now a flat light-green fill with white
    text and no dark shadow plate, fixing the two-tone green CONTINUE button.
2026-05-31 MCR Phase 2: professor instructions + hand separation
    Turn a merged score into a musician-style, step-by-step lesson instead of a
    flat note dump.
    Schema (src/lessons/schema.ts) — additive, back-compatible:
    - HandName + `hand` on chord/seq/arpeggio (left=violet, right=cyan, both=green).
    - New `count` segment (rhythm counting for the meter) and `arpeggio` segment
    (roll a chord low->high, "rai not tu hop am").
2026-06-01 ci: build APK on the redesign branch too
    Lets the EAS preview (APK) workflow run for the Phase 1 redesign branch so
    it can be installed and tested before merging to main.
2026-06-10 Multi-page OMR: whole-song MusicXML, falling-notes player, Firebase library
    Klang.io-style sheet-music import:
    - Pick/photograph every page of a song; each page runs through the oemer
    OMR server and the per-page MusicXML is merged into ONE score
    (src/omr/mergeMusicXml.ts, measures appended + renumbered per part).
    - New timed MusicXML parser (src/omr/musicxmlScore.ts) handling divisions,
    tempo, <chord/>, <backup>/<forward> voices, staffs and ties.
2026-06-10 Musical post-correction + notation review screen (klang.io steps 3+4)
    Step 3 — musical sanity pass:
    - backend/omr/postprocess.py (music21): drops notes outside the piano's
    A0..C8 range (replaced with equal-length rests so measure math holds),
    quantizes onsets/durations to a 16th+triplet grid to stop OMR duration
    drift, rebuilds notation. Best-effort with raw-XML fallback; applied
    after merging in /omr and /omr/score. OMR_POSTPROCESS=0 disables.
2026-06-10 QC fixes: stack chord voicings up from the root; drop dead code; v0.7.0
    - detectChords voiced triads C3..B3 by pitch class, so chords like G
    major came out G3-B3-D3 (the fifth BELOW the root) — and the chord
    quiz would reject a student correctly playing G3-B3-D4 with 5-3-1.
    Now stacked root-up; regression test added.
    - Removed unused single-image picker path from the import screen.
    - Bump to 0.7.0 / versionCode 8 for the new APK.
2026-06-10 Version design drops under designs/v2; fresh repo README; CI paths
    - project/, chats/ and the handoff README move to designs/v2/ (one dir
    per design version so weekly drops diff cleanly)
    - new root README documents the shells/drops/contract architecture
    - EAS workflow paths-ignore updated for the new layout
    https://claude.ai/code/session_01JqK2zv6c6AhLTdabTpPsQw
2026-06-10 Adopt design-CSS color values as authoritative in v2 theme
    Colors now derive from tokens.generated.ts. Corrects 8 values that had
    drifted from the V2 design spec (cream50/100, ink700/500/300, inkLine,
    butterDark, skyDark) and exposes the full design palette (cream200/300,
    brandDeep/Soft, rustDark, coral, plum, leaf, staff, piano black/white).
    RN-only extras (status, dark stage, gradients, shadows) stay hand-tuned.
    https://claude.ai/code/session_01JqK2zv6c6AhLTdabTpPsQw
2026-06-10 Add render-every-screen smoke tests for the active UI shell
    - jest multi-project: 'logic' (node unit tests) + 'ui' (jest-expo)
    - manual mocks for all native modules (BLE, audio, speech, haptics,
    orientation, notifications, image picker, fonts, AsyncStorage)
    - harness mounts screens inside real providers + navigator, the way the
    app does; registry completeness check fails if a screen file is ever
    added without smoke coverage
